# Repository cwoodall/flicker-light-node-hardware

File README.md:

# flicker-lights-node-hardware

Electrical and mechanical hardware designs for the Flicker Light Nodes, which use the ATMega168 and NRF24L01.

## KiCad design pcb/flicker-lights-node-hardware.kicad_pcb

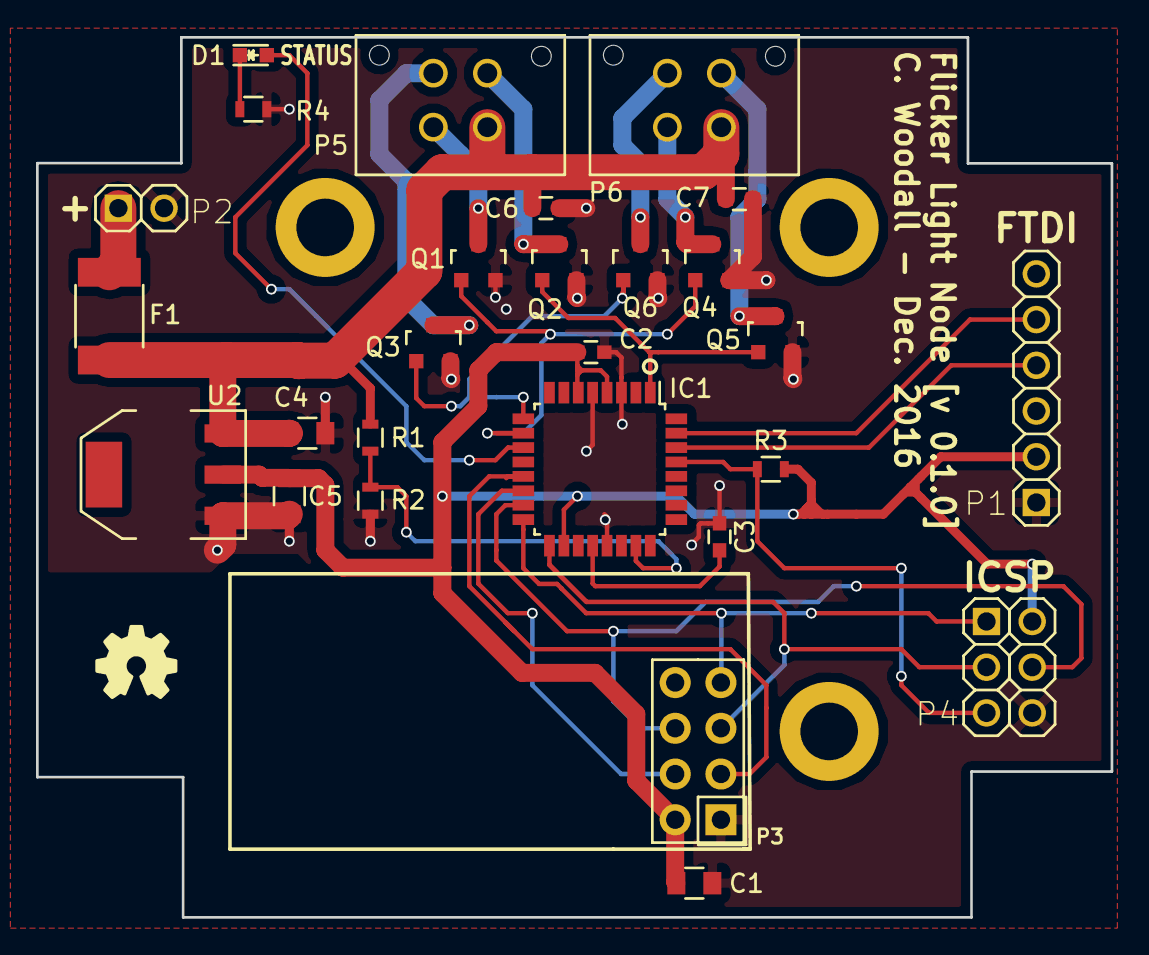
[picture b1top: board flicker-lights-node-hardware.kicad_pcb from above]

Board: 2 copper layers, 59.7 x 48.9 mm, 27 parts (0 on the bottom side), 25 nets.

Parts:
C1, C4, C5: 4.7uF; C_0805
C2, C3, C6, C7: .1uF; C_0603
D1: GREEN; LED_0603
F1: PTC RESTTBLE 2.6A 16V CHIP 1812; R_1812
IC1: ATMEGA168PA-A; LQFP-32_7x7mm_Pitch0.8mm
P1: CONN_01X06; HDR_1x6
P2: CONN_01X02; HDR_1x2
P3: CONN_02X04; NRF24L01
P4: CONN_02X03; HDR_2x3
P5, P6: CONN_01X04; Molex_Microfit3_Header_02x02_Straight_43045-0428
Q1, Q2, Q3, Q4, Q5, Q6: BSS138; SOT-23
R1: 200K; R_0603
R2: 100K; R_0603
R3: 10K; R_0603
R4: 1K; R_0603
U2: LD1117S33CTR; SOT-223

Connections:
+3V3: C1.1, C2.1, C5.1, IC1.4, IC1.6, IC1.18, P1.2, P3.2, P4.2, R3.1, U2.2
+9V: C4.1, C6.1, C7.1, F1.2, P5.1, P6.1, R1.1, U2.3
/FTDI_RX: IC1.30, P1.4
/FTDI_TX: IC1.31, P1.5
/LED_BLUE: IC1.1, Q2.1, Q5.1
/LED_GREEN: IC1.10, Q1.1, Q4.1
/LED_RED: IC1.9, Q3.1, Q6.1
/NRF24_CE: IC1.13, P3.3
/NRF24_CSN: IC1.14, P3.4
/NRF24_MI: IC1.16, P3.7, P4.1
/NRF24_MO: IC1.15, P3.6, P4.4
/NRF24_SCK: IC1.17, P3.5, P4.3
/VADC: IC1.23, R1.2, R2.1
GND: C1.2, C2.2, C3.2, C4.2, C5.2, C6.2, C7.2, IC1.3, IC1.5, IC1.21, P1.1, P2.2, P3.1, P4.6, Q1.2, Q2.2, Q3.2, Q4.2, Q5.2, Q6.2, R2.2, R4.2, U2.1
unnamed: C3.1, IC1.20
unnamed: D1.1, R4.1
unnamed: D1.2, IC1.11
unnamed: F1.1, P2.1
unnamed: IC1.29, P4.5, R3.2
unnamed: P5.2, Q1.3
unnamed: P5.3, Q2.3
unnamed: P5.4, Q3.3
unnamed: P6.2, Q4.3
unnamed: P6.3, Q5.3
unnamed: P6.4, Q6.3

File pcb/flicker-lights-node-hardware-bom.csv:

Reference,Value,Quantity,Supplier,Supplier Part Number,Manufacturer,Manufacturer Part Number
P5;P6,CONN_01X04,2,Digikey,WM1814-ND,Molex,0430450400
U2,LD1117S33CTR,1,Digikey,497-1240-1-ND,STMicroelectronics,LD1117S25CTR
P2,CONN_01X02,1,,,,
R3,10K,1,Digikey,311-10KGRCT-ND,Yageo,RC0603JR-0710KL
P4,CONN_02X03,1,Digikey,952-2121-ND,Harwin Inc.,M20-9980346
C3;C2;C7;C6,.1uF,4,Digikey,311-1343-1-ND,Yageo,CC0603ZRY5V9BB104
Q6;Q5;Q4;Q3;Q2;Q1,BSS138,6,Digikey,BSS138LCT-ND,ON Semiconductor,BSS138L
D1,GREEN,1,Digikey,160-1475-1-ND,Light-On,LTST-S270GKT
R4,1K,1,Digikey,311-1.0KGRCT-ND,Yageo,RC0603JR-071KL
R1,200K,1,Digikey,311-200KGRCT-ND,Yageo,RC0603JR-07200KL
R2,100K,1,Digikey,311-100KGRCT-ND,Yageo,RC0603JR-07100KL
P1,CONN_01X06,1,,,,
P3,CONN_02X04,1,Digikey,S7072-ND,Sullins Connector Solutions,PPTC042LFBN-RC
F1,PTC RESTTBLE 2.6A 16V CHIP 1812,1,Digi-Key,507-1780-1-ND,Bel Fuse Inc.,0ZCG0260BF2B
C1;C4;C5,4.7uF,3,Digikey,490-3335-1-ND,Murata,GRM21BR61E475KA12L
U1,NRF24L01_MODULE,1,Amazon,LD1117S25CTR,Slou,BC19422
IC1,ATMEGA168PA-A,1,Digikey,ATMEGA168PA-AU-ND,Atmel,ATMEGA168PA-AU

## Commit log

2016-12-26 First readme
2016-12-26 First commit of Schematic
2016-12-26 Finished up first draft of schematic, finding all parts, debating switch, or if I should just make users disconnect battery, I know the right answer, but only have so much space... I am thinking to m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
2016-12-26 Added project box part so it is included on BOM
2016-12-26 Deployed 2c3abb6 with MkDocs version: 0.16.1
2016-12-26 Renamed from flicker-light to flicker-lights
2016-12-27 First layout attempt done, new board outline with better dimensioning. Added a preview picture.
2016-12-27 Finished cleaning up silkscreen
2016-12-27 Added script for generating BOM (from https://productize.be/kicad-bom-generation/), and added BOM
2016-12-27 Cleaned up genbom script
2016-12-27 Updated bom with new genbom script
2016-12-27 Removed copper from underneath radio module
2016-12-27 Prepared release 0.1.0 of flicker-lights-node-hardware as released
2016-12-27 Deployed 184692c with MkDocs version: 0.16.1
2016-12-27 updated history file with a warning about the order information
2016-12-27 Deployed aa29737 with MkDocs version: 0.16.1
2017-01-12 Made IC1 pin 1 more obvious on the PCB silkscreen
    Fixes #1
2017-01-20 do to a cabling error swapped R and B leds. Need to propagate to FW

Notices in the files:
pcb/flicker-lights-node-hardware.kicad_pcb:
CC BY 4.0
